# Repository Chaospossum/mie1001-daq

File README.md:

# MIE1001 Team 5&4 — data acquisition for the portable quadrupole mass spectrometer

Foundation of Imaging Engineering (MIE1001), Maastricht University, 2026.
Team 5 owns the data chain: detector signal → preamp → ADC → Arduino UNO → laptop, plus the DAC that
sends the mass command to the Extrel 150-QC quadrupole controller.

```
Faraday cup ─► preamp (LMP7721, 100 MΩ) ─► ADS1115 16-bit ADC ─I²C─► Arduino UNO ─USB─► laptop
                                               MCP4725 12-bit DAC ◄─I²C─┘ ─► mass command (0-5 V now; Extrel wants 0-10 V)
```

## Contents

| Folder | What |
|---|---|
| `firmware/` | Arduino sketches (open in the Arduino IDE; board: Arduino Uno) |
| `hardware/mie1001_daq_simple/` | **Simple shield, rev E**: plug-in ADS1115 + MCP4725 breakouts, screw terminals, and the Faraday-cup preamp. Ordered from Digi-Key and hand-soldered. See its README |
| `hardware/mie1001_daq_board/` | **Full shield, rev E**: everything soldered (ADS1115, MCP4725, preamp), BNC input, CEM/Faraday ranges |
| `hardware/enclosure/` | First idea for a 3D-printed enclosure (transparent PETG, OpenSCAD source, STLs, renders). Not printed, not a team decision yet |
| `wokwi/` | Wokwi simulation of the whole loop: Uno → MCP4725 → quadrupole stand-in → ADS1115, with custom chips written in C and a PEG1000 test spectrum |
| `data/` | Real measurements (`2026-09-20_selftest/`: first self-tests of the ADS1115 and MCP4725 on the Uno, with plots) and clearly labelled simulations (`simulations/`) |

### Firmware

| Sketch | Tests | For | Serial |
|---|---|---|---|
| `DAQ_shield_scan` | **Mass scan**: DAC code sweep on QPS OUT, preamp current (A1−A3) with 50 Hz window averaging, A2 command read-back (JP1), zero/offset, trigger on D8, self-check (`i`) | **shield** (rev E) | 115200 |
| `DAQ_loopback_test` | DAC → ADC loopback (wire QPS OUT to SIGNAL IN) | **shield** | 115200 |
| `DAQ_mini_chain` | Chain: DAC → UNO A0 → PWM D9 → RC filter → ADS1115. Assumes ADS A1 = DAC; on the shield A1 is PRE_OUT | **breadboard only** | 115200 |
| `ADS1115_selftest` | ADS1115 alone: reads the UNO's 3.3 V, GND and 5 V pins | breadboard | 9600 |
| `MCP4725_standalone_test` | MCP4725 alone, read back on the UNO's A0; scans the I²C bus if not found | breadboard | 9600 |
| `MCP4725_sine_scope` | MCP4725 sine wave, sent vs. read on the Serial Plotter | breadboard | 115200 |
| `SparkFun_MCP4725_waveform` | SparkFun's 512-point sine example (J. Bartlett, 2014, beerware). Its A2/A3 power trick is for a bare breakout on the UNO header, not the shield | breadboard (shield: drop the A2/A3 lines) | — |
| `ioannis_DAC_3V` | Ioannis's sketch: holds the MCP4725 (0x60) at 3 V. Now measures the real 5 V rail first (internal bandgap), since a fixed code 2457 gave ~2.9 V on USB | either | 115200 |
| `PwmGenerator` | Two-channel PWM generator on pins 9/10 (bench tool, not DAQ) | bench | 115200 |

Libraries: Adafruit ADS1X15, Adafruit MCP4725. I²C addresses: ADS1115 0x48, MCP4725 0x60.

### Hardware

Both boards are **generated by Python** (`generate_schematic.py`, `generate_pcb.py`); `./build.sh` rebuilds the
KiCad files, runs ERC, DRC (with schematic parity) and the preamp guard check, and writes the fab files in
`fab/` (gerbers, Digi-Key BOM; the JLCPCB files are optional leftovers). Edits made in the KiCad GUI are overwritten by the next build. Needs KiCad 10 (flatpak `org.kicad.KiCad`).
The simple board's PCB script reuses the router in `../mie1001_daq_board/`, so keep both folders side by side.

## Status (2026-09-25)

- Firmware: all sketches compile for the UNO. The self-tests pass on the real Uno (see `data/`);
  `DAQ_shield_scan` is untested until the shield is soldered.
- Simple shield rev E: fixes from an independent design review (closed guard ring under the LMP7721, mask-free
  guard, 100k/100k VREF divider, A4/A5 wired, JP1 mass-command read-back). ERC, DRC and guard check clean.
  Not yet ordered. Everything is ordered from Digi-Key and soldered by hand. Do a 1:1 paper print check on a real UNO first.
- Open: the Extrel 150-QC mass command is 0-10 V (a x2 stage with its own supply is still needed) and its
  volts-per-amu scaling is unconfirmed.

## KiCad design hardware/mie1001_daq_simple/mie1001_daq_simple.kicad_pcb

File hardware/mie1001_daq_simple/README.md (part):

# MIE1001 — simple DAQ shield (rev E)

The beginner version of the DAQ board: an Arduino UNO R3 shield that the two breakout
boards from class plug into (modular: both unplug). Fat tracks, the breakouts, connectors and
through-hole parts are hand-soldered. **Rev D adds a Faraday-cup preamp** with 16 small SMD parts.
**Everything is ordered from Digi-Key** (university procurement, see [Ordering from Digi-Key](#ordering-from-digi-key))
**and hand-soldered** (see [Hand-soldering order](#hand-soldering-order)); JLCPCB assembly is an optional alternative.

```
SIGNAL IN (J1) -> R2 4k7 -> [CR1/CR2 clamp, C1 filter] -> ADS1115 breakout A0 -> I2C -> UNO -> USB -> laptop
UNO -> I2C -> SparkFun MCP4725 breakout OUT -> QPS OUT (J2), 0-5 V  (JP1, bridged: also -> ADS1115 A2 read-back)
TRIG IN (J3) -> R1 1k -> UNO D8 (R3 100k to GND)    ADS1115 ALRT -> UNO D2
Faraday cup -> J5 SMA -> R4 10k -> CR3 clamp to VREF -> R5 1k -> U3 LMP7721 preamp (R6 100M || C2 10p)
            -> R11/C6 1k/1u -> ADS1115 A1 (PRE_OUT)      VREF 2.5 V (R8/R9 100k/100k + C4 -> U4A MCP6002 -> R10 -> C5) -> A3
J4 = test header: 1 PRE_OUT, 2 A2 (QPS read-back while JP1 is bridged), 3 VREF, 4 GND
I2C: UNO SDA/SCL header pins AND A4/A5 (rev E)
```

| Check | Result |
|---|---|
| ERC | 0 errors, 0 warnings |
| Guard check (`check_guard.py`, rev E) | PASS: 0 items of any other net within 1.0 mm of the preamp input (COAX_IN, DET_IN, TIA_IN, TIA_REF), every input item has guard copper within 0.6 mm, and the bare-board flood fill from the input reaches only VREF and TIA_OUT on F.Cu and only VREF on B.Cu. The same script FAILS on the rev D board (7 leakage paths), so it catches the rev D defect |
| Independent critical review | Two reviews against the Adafruit, SparkFun, Arduino, Phoenix and TI source files and datasheets. Rev A: pinouts and UNO geometry correct, four fixes → rev B. Rev C: copper clean, no respin needed; one wrong BOM part number and several wrong claims in this file, all corrected below |
| Host board | Arduino UNO R3 **SMD** (ATmega328P in a flat TQFP-32 package). Its headers are identical to the standard R3 (same positions, same pins, SDA/SCL next to AREF), so the shield fits unchanged |
| Still unverified | The height of the parts on the UNO under the shield (crystal, USB chip, capacitors). The SMD chip itself is only about 1.2 mm tall, so this is much less of a risk than with the socketed DIP chip, but look at your board before soldering |
| DRC incl. schematic parity | 0 errors, 0 unconnected, 0 parity issues (4 `lib_footprint_mismatch` warnings: ARD1 and J1–J3 are deliberately modified copies) — rev E |
| Orientation | Same real-UNO geometry as the full board (rev E): flipped library footprint, keep-outs over the USB, DC jack and both ICSP headers |
| Rules | 0.5 mm tracks, ≥ 0.3 mm gaps, 0.8/0.4 mm vias: far above the Digi-Key PCB Builder (5 mil / 8 mil) and JLCPCB minimums |

## What changed in rev E (2026-09-25)

An independent review of rev D found a leakage path and a few smaller problems. **No connector,
socket or mounting hole moved** (J1–J5, the two breakout sockets, H1–H3 are where they were in rev D).
The router re-laid most of the signal tracks because the obstacles changed; that does not matter
electrically, DRC and the guard check are clean.

- **Guard closed under U3.** In rev D the guard pour stopped halfway under the LMP7721, and TIA_OUT
  ran from the feedback parts under the chip body to pin 4. The copper-free gap alongside it was a
  bare-board path from the input to GND (pin 3) and +5V (pin 6). Now a VREF bar runs under the
  chip from pin 2 to pin 7 (both N/C pins, on the guard), so the input pins 1 and 8 sit in a closed
  guard pocket, and TIA_OUT leaves the guard on the **bottom layer only**: via next to R6/C2, under
  the chip, via below the bar, then to pin 4 and R11. On the top layer the input is now completely
  surrounded by guard copper; the only other net it faces is TIA_OUT across C2 and R6 themselves,
  which only adds in parallel with the feedback resistor (TI LMP7721 datasheet, 10.1).
  DET_IN was re-laid as two straight runs so the guard hugs it everywhere.
- **No solder mask on the guard (both layers).** The mask openings are the guard pour shrunk by
  0.10 mm and kept ≥ 0.50 mm from any pad and ≥ 0.40 mm from any track of another net, and off all
  silkscreen. So every other track, every gap next to the guard and the edge of the GND pour stay
  under mask: exposed guard copper is never closer than 0.4 mm (mask web) to exposed copper of
  another net, which keeps solder bridges unlikely. Care points: the SMA J5 ground pins sit next to
  the bare guard ring around the centre pin (≥ 0.5 mm mask web); don't flood them with solder, and
  check there is no bridge from a J5 ground pin to the ring before powering up.
- **`check_guard.py` is strict now.** It fails (exit 1) on any unguarded input item (it used to only
  print them) and adds a bare-board flood fill from the input nets on each copper layer: reaching
  copper of any net other than VREF / TIA_OUT, or leaving the guard area, fails the build.
  `check_guard.py .history/revD-final/mie1001_daq_simple.kicad_pcb` shows the rev D failure.
- **Quieter VREF.** R8/R9 are now 100k/100k (were 10k/10k). With C4 10 µF the divider's corner is
  0.32 Hz instead of 3.2 Hz, so 50 Hz ripple on the USB 5 V reaches VREF attenuated ~160× instead
  of ~16×. The MCP6002's ~1 pA input bias current makes no measurable error through 50k.
- **A4/A5 also carry SDA/SCL.** On a genuine UNO R3 they are the same signals as the SDA/SCL pins
  next to AREF; some clones don't have those two pins, and then the shield works through A4/A5.
  Consequence: **never use A4/A5 as analog inputs** with this shield fitted.
- **JP1, QPS read-back.** A solder jumper, bridged by a copper strip from the factory, connects
  QPS OUT (MCP4725 OUT, J2) to ADS1115 **A2** (J4 pin 2). The firmware can read the command voltage
  it actually set: `ads.readADC_SingleEnded(2)`, with the ±6.144 V range
  (`ads.setGain(GAIN_TWOTHIRDS)`), because 0–5 V does not fit the ±4.096 V range. To use A2 for something else, cut the thin copper
  bridge between JP1's pads with a knife (check with a meter); a blob of solder closes it again.
  JP1 is next to J4, marked "JP1 / A2=QPS".
- **C5/C6 part (optional JLC route only).** LCSC C15849 had no LCSC stock; now C5673 (Samsung CL10A105KA8NNNC, 1 µF 25 V X5R
  0603, extended part: one extra JLC loading fee). There is no other *basic* 1 µF 0603 at JLC;
  JLC's own library still listed C15849 in stock on 2026-09-25, so it is a valid fallback.
- **Docs:** J4 firmware note rewritten (pins 1 and 3 are op-amp outputs), wrong 8 SPS/mains claim
  corrected, comparison with the full board corrected, U3 "no solder mask" note is now true.

## What changed in rev D (2026-09-24): the preamp

The Faraday cup gives a current of pA to nA. The ADS1115 measures voltage, so rev D adds a
**transimpedance amplifier** (U3, LMP7721) that turns 1 nA into 0.1 V. Everything that was on rev C
stays where it was; the preamp sits in the band under the digital header, where the text used to be
(the text moved to the left edge and the back).

| Part | Job |
|---|---|
| **J5** SMA jack (vertical, PTFE) | Detector input. Use a **BNC-female to SMA-male adapter** for a BNC cable. A BNC did not fit anywhere on this board |
| **U3** LMP7721 + **R6** 100 MΩ | The preamp: Vout = VREF − I × 100 MΩ. Full scale ~25 nA; 1 ADC count = 1.25 pA at GAIN_ONE |
| **C2** 10 pF | Stops the preamp oscillating with the cable capacitance. Sets a 159 Hz bandwidth |
| **R4** 10k + **CR3** BAV199 + **R5** 1k | Protect U3 from a discharge on the cable. CR3 is tied to VREF, so it leaks ~0 into the input |
| **VREF** 2.5 V: R8/R9 100k/100k (rev E), C4 10 µF, U4A MCP6002, R10 100 Ω, C5 1 µF | The input sits at 2.5 V so the output can swing both ways on a single 5 V supply |
| **R7** 1k | Protects U3's + input |
| **R11** 1k + **C6** 1 µF | 159 Hz anti-alias filter before ADS1115 **A1** |
| **Guard ring** (copper at VREF, both layers, no solder mask) | Surrounds the whole input so no other copper can leak pA into it; closed under U3 between pins 2 and 7 (rev E) |

**Firmware:** read the preamp as `ads.readADC_Differential_1_3()` (A1 − A3 = PRE_OUT − VREF), then
`I = −V / 100e6`. The ADS1115 only offers the pairs 0-1, 0-3, 1-3 and 2-3, which is why VREF is on A3.
SIGNAL IN (J1) → A0 still works as before for a voltage input.

**J4 changed:** pin 1 is now PRE_OUT and pin 3 is VREF (monitor only: connect a meter or scope, never a
source). Pin 2 (A2) carries the QPS read-back while JP1 is bridged (rev E); cut JP1 to use it as a free input.

**Still 0-5 V on QPS OUT.** The Extrel 150-QC wants a 0-10 V mass command; that needs a gain-2 amplifier on
a supply above 10 V (e.g. a 12 V adapter on the UNO's DC jack). Not on this revision.

**Handling:** the input works at picoamps. After soldering, wash off **all** flux around U3, R6, C2, R4 and
J5 (isopropyl alcohol, then dry), handle the board by its edges, and measure the zero offset with the
cable connected and the beam off before every scan.

## Names on the drawing and the board (2026-09-24, copper unchanged)

- The UNO is **ARD1** and the clamp diodes are **CR1, CR2** (were A1, D1, D2), so the names no longer clash
  with the UNO's pins A1 and D2.
- The UNO symbol shows only the pin names printed on the UNO (D2, D8, SDA ...), not KiCad pad numbers.
- SDA/A4 and SCL/A5 are the same signals on the UNO R3. Since rev E the shield connects A4/A5 as well
  (for clones without the SDA/SCL pins), so never use A4 and A5 as analog inputs.

## What changed in rev C

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
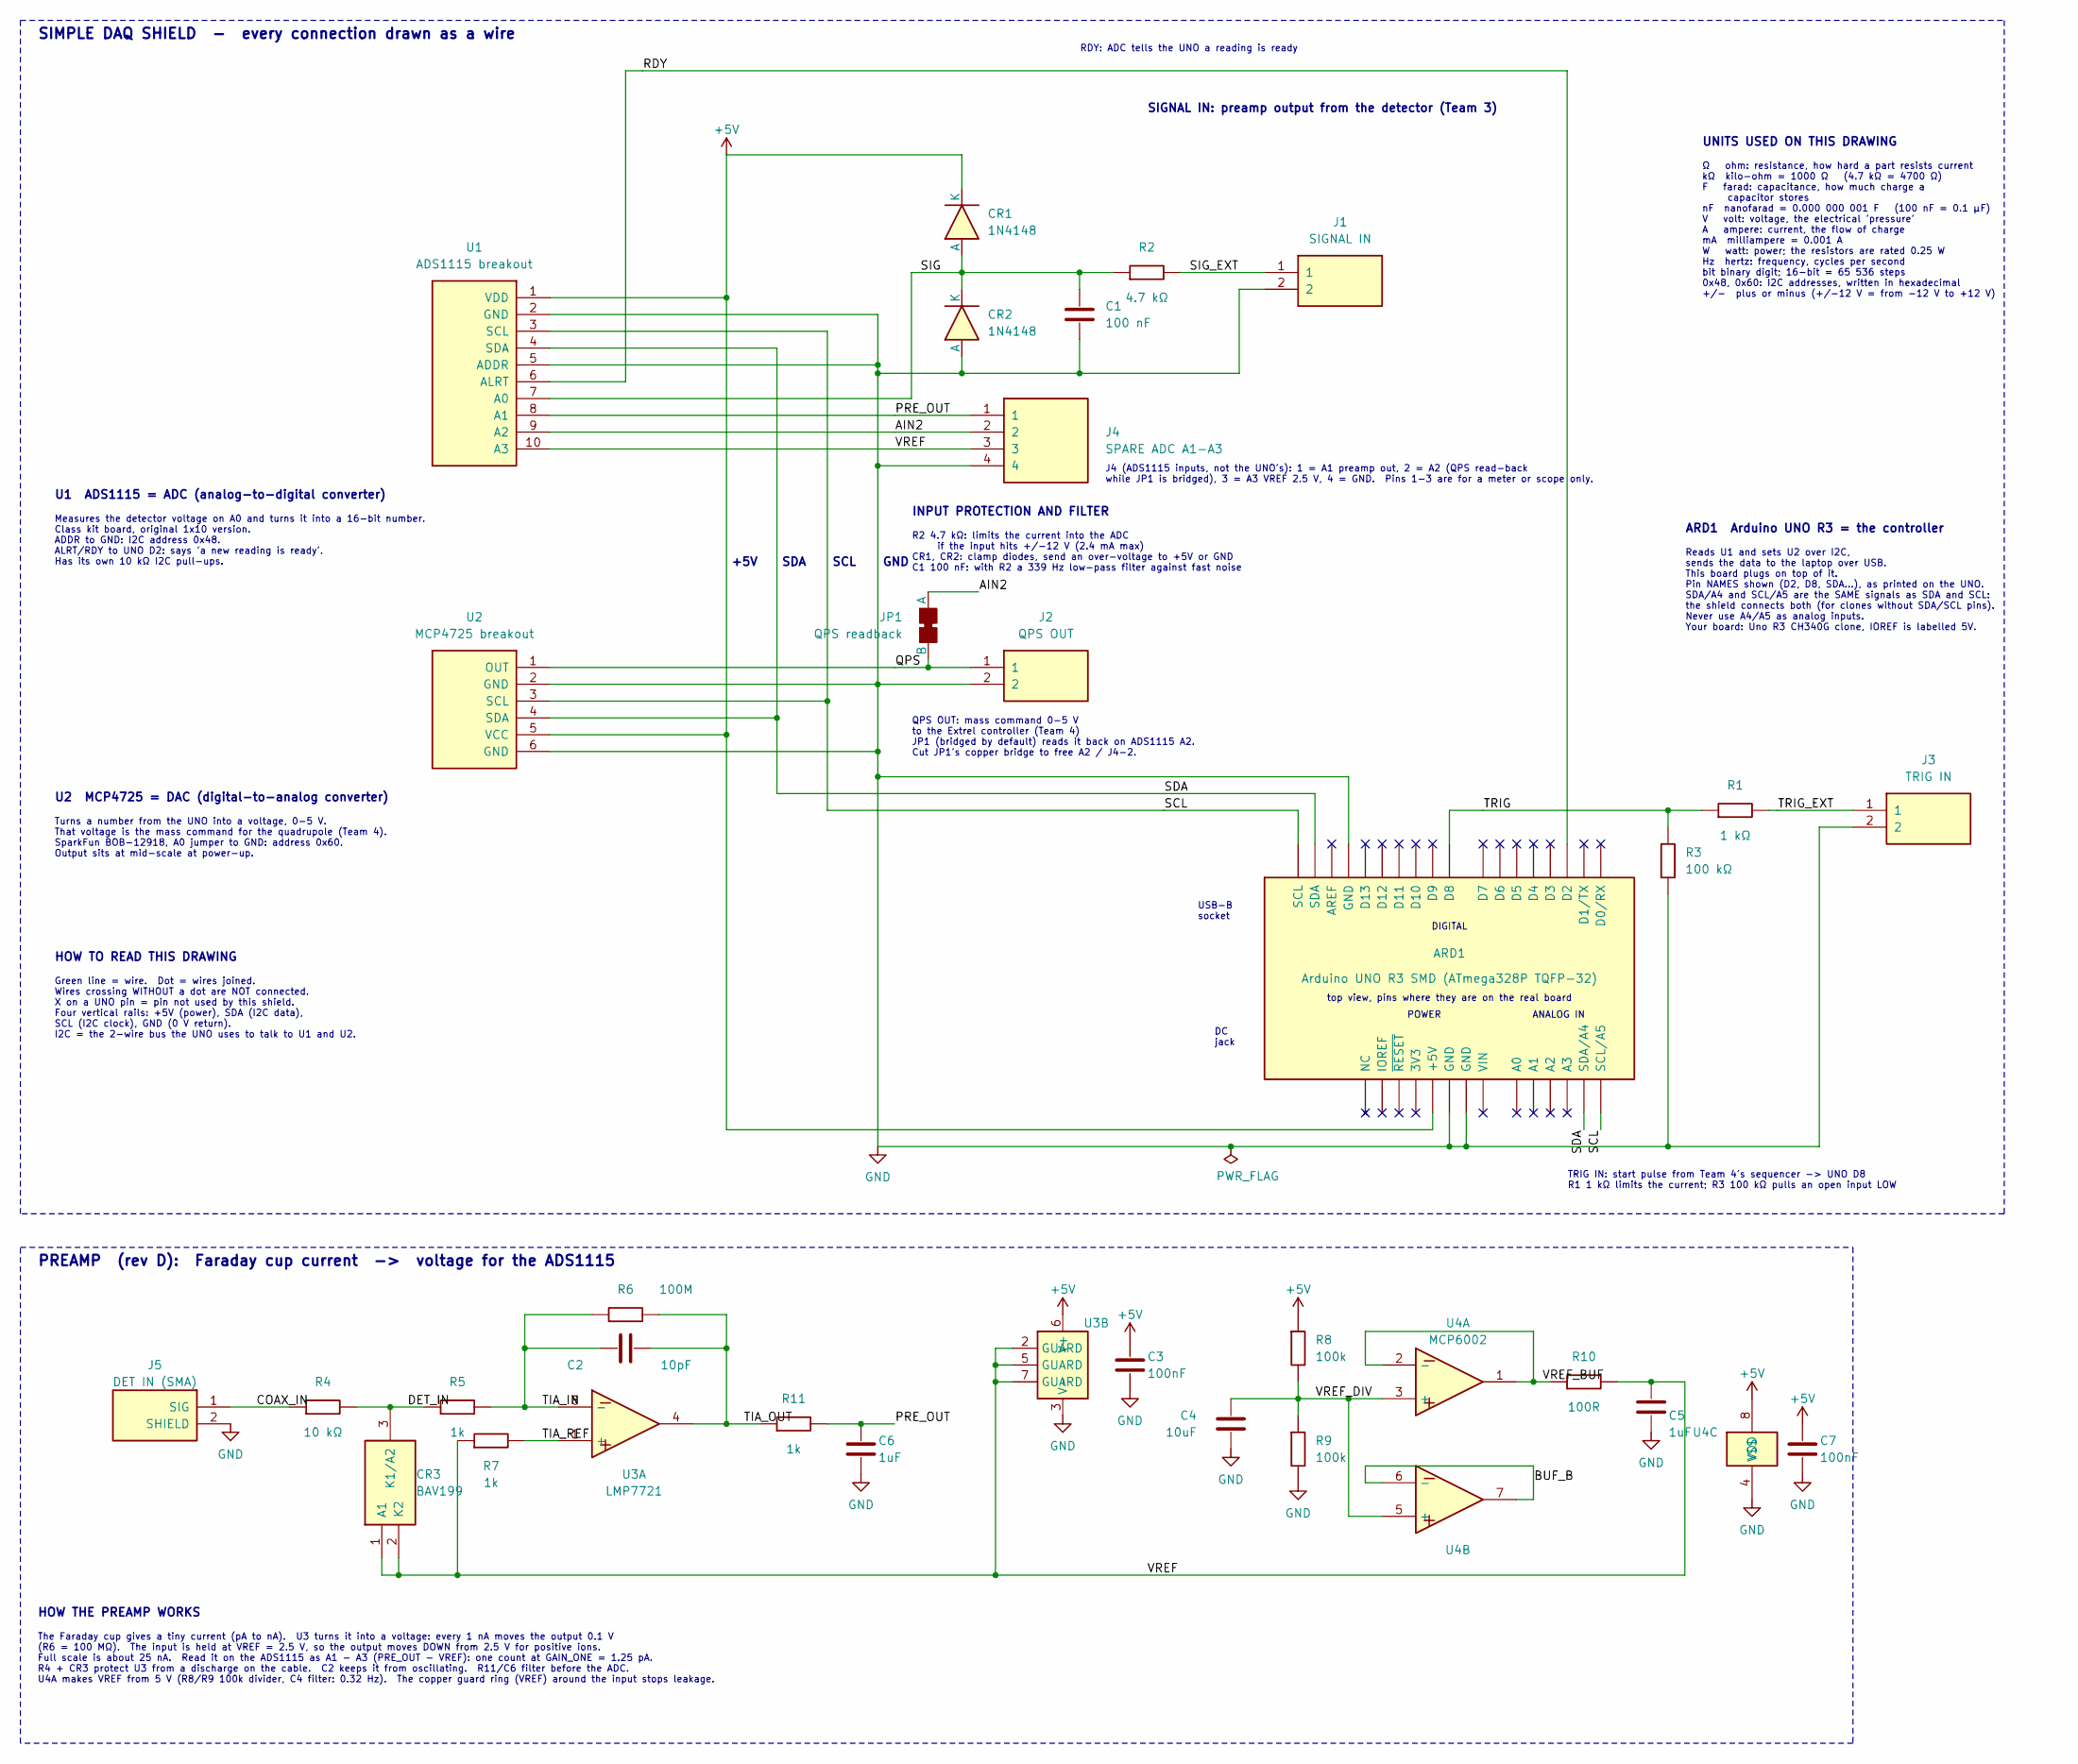
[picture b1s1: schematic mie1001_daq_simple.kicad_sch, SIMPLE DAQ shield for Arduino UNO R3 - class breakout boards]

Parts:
ARD1: Arduino UNO R3 SMD (ATmega328P TQFP-32); Arduino_UNO_R3; Rating Arduino UNO R3 SMD (ATmega328P TQFP-32); MPN UNO R3 SMD CH340 clone (marked V1888); 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; Digi-Key P/N do not order: use your own board
C1: 100 nF; C_Disc_D5.0mm_W2.5mm_P2.50mm; Rating 100 nF 50 V X7R ceramic; MPN K104K15X7RF5TL2; Digi-Key P/N BC1084CT-ND
C2: 10pF; C_0603_1608Metric; Rating 10pF C0G 50V 0603; MPN CL10C100JB8NNNC; Digi-Key P/N 1276-1027-1-ND
C3, C7: 100nF; C_0603_1608Metric; Rating 100nF X7R 50V 0603; MPN 885012206095; Digi-Key P/N 732-8013-1-ND
C4: 10uF; C_0805_2012Metric; Rating 10uF X5R 25V 0805; MPN TMK212BBJ106KGHT; Digi-Key P/N 587-4334-1-ND
C5, C6: 1uF; C_0603_1608Metric; Rating 1uF X5R 25V 0603; MPN CL10A105KA8NNNC; Digi-Key P/N 1276-1102-1-ND
CR1, CR2: 1N4148; D_DO-35_SOD27_P7.62mm_Horizontal; Rating 1N4148; MPN 1N4148; Digi-Key P/N 1N4148FS-ND
CR3: BAV199; SOT-23; Rating BAV199LT1G; MPN BAV199LT1G; Digi-Key P/N BAV199LT1GOSCT-ND
J1: SIGNAL IN; TerminalBlock_Phoenix_PT-1,5-2-3.5-H_1x02_P3.50mm_Horizontal; Rating Signal in; MPN 1984617; Digi-Key P/N 277-1721-ND
J2: QPS OUT; TerminalBlock_Phoenix_PT-1,5-2-3.5-H_1x02_P3.50mm_Horizontal; Rating QPS out; MPN 1984617; Digi-Key P/N 277-1721-ND
J3: TRIG IN; TerminalBlock_Phoenix_PT-1,5-2-3.5-H_1x02_P3.50mm_Horizontal; Rating Trigger in; MPN 1984617; Digi-Key P/N 277-1721-ND
J4: SPARE ADC A1-A3; PinSocket_1x04_P2.54mm_Vertical; Rating Spare ADC in; MPN PPTC041LFBN-RC; Digi-Key P/N S7002-ND
J5: DET IN (SMA); SMA_Amphenol_132134_Vertical; Rating Detector in, SMA jack vertical; MPN 132134; Digi-Key P/N ACX1230-ND
JP1: QPS readback; SolderJumper-2_P1.3mm_Bridged_RoundedPad1.0x1.5mm
R1: 1 kΩ; R_Axial_DIN0207_L6.3mm_D2.5mm_P10.16mm_Horizontal; Rating 1 kOhm 0.25 W; MPN CFR-25JB-52-1K; Digi-Key P/N 1.0KQBK-ND
R2: 4.7 kΩ; R_Axial_DIN0207_L6.3mm_D2.5mm_P10.16mm_Horizontal; Rating 4.7 kOhm 0.25 W; MPN CFR-25JB-52-4K7; Digi-Key P/N 13-CFR-25JB-52-4K7-ND
R3: 100 kΩ; R_Axial_DIN0207_L6.3mm_D2.5mm_P2.54mm_Vertical; Rating 100 kOhm 0.25 W; MPN CFR-25JB-52-100K; Digi-Key P/N 13-CFR-25JB-52-100K-ND
R4: 10 kΩ; R_Axial_DIN0207_L6.3mm_D2.5mm_P2.54mm_Vertical; Rating 10 kOhm 0.25 W; MPN CFR-25JB-52-10K; Digi-Key P/N 13-CFR-25JB-52-10K-ND
R5, R7, R11: 1k; R_0603_1608Metric; Rating 1k 1% 0603; MPN RC0603FR-071KL; Digi-Key P/N 311-1.00KHRCT-ND
R6: 100M; R_1206_3216Metric; Rating 100M 1% 1206; MPN HVCB1206FKC100M; Digi-Key P/N HVCB1206FKC100MCT-ND
R8, R9: 100k; R_0603_1608Metric; Rating 100k 1% 0603; MPN RC0603FR-07100KL; Digi-Key P/N 311-100KHRCT-ND
R10: 100R; R_0603_1608Metric; Rating 100R 1% 0603; MPN RC0603FR-07100RL; Digi-Key P/N 311-100HRCT-ND
U1: ADS1115 breakout; PinSocket_1x10_P2.54mm_Vertical; Rating Adafruit ADS1115 breakout (original, 1x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; MPN 1085 (ORIGINAL 1x10 version, from the c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; Digi-Key P/N do not order
U2: MCP4725 breakout; PinSocket_1x06_P2.54mm_Vertical; Rating SparkFun MCP4725 breakout; MPN 12918; Digi-Key P/N 1568-12918-ND
U3: LMP7721; SOIC-8_3.9x4.9mm_P1.27mm; Rating LMP7721MA/NOPB; MPN LMP7721MA/NOPB; Digi-Key P/N LMP7721MA/NOPB-ND
U4: MCP6002; SOIC-8_3.9x4.9mm_P1.27mm; Rating MCP6002-I/SN; MPN MCP6002-I/SN; Digi-Key P/N MCP6002-I/SN-ND

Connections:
+5V: ARD1.5 (+5V), C3.1, C7.1, CR1.1 (K), R8.1, U1.1 (VDD), U2.5 (VCC), U3.6 (V+), U4.8 (VDD)
/AIN2: J4.2, JP1.1 (A), U1.9 (A2)
/BUF_B: U4.6 (-), U4.7
/COAX_IN: J5.1 (SIG), R4.1
/DET_IN: CR3.3 (K1/A2), R4.2, R5.1
/PRE_OUT: C6.1, J4.1, R11.2, U1.8 (A1)
/QPS: J2.1, JP1.2 (B), U2.1 (OUT)
/RDY: ARD1.17 (D2), U1.6 (ALRT)
/SCL: ARD1.14 (SCL/A5), ARD1.32 (SCL), U1.3 (SCL), U2.3 (SCL)
/SDA: ARD1.13 (SDA/A4), ARD1.31 (SDA), U1.4 (SDA), U2.4 (SDA)
/SIG: C1.1, CR1.2 (A), CR2.1 (K), R2.1, U1.7 (A0)
/SIG_EXT: J1.1, R2.2
/TIA_IN: C2.1, R5.2, R6.1, U3.8 (-)
/TIA_OUT: C2.2, R6.2, R11.1, U3.4
/TIA_REF: R7.2, U3.1 (+)
/TRIG: ARD1.23 (D8), R1.1, R3.1
/TRIG_EXT: J3.1, R1.2
/VREF: C5.1, CR3.1 (A1), CR3.2 (K2), J4.3, R7.1, R10.2, U1.10 (A3), U3.2 (GUARD), U3.5 (GUARD), U3.7 (GUARD)
/VREF_BUF: R10.1, U4.1, U4.2 (-)
/VREF_DIV: C4.1, R8.2, R9.1, U4.3 (+), U4.5 (+)
GND: ARD1.6 (GND), ARD1.7 (GND), ARD1.29 (GND), C1.2, C3.2, C4.2, C5.2, C6.2, C7.2, CR2.2 (A), J1.2, J2.2, J3.2, J4.4, J5.2 (SHIELD), R3.2, R9.2, U1.2 (GND), U1.5 (ADDR), U2.2 (GND), U2.6 (GND), U3.3 (V-), U4.4 (VSS)

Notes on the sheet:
SIMPLE DAQ SHIELD - every connection drawn as a wire
USB-B socket
DC jack
top view, pins where they are on the real board
POWER
ANALOG IN
DIGITAL
U1 ADS1115 = ADC (analog-to-digital converter)
Measures the detector voltage on A0 and turns it into a 16-bit number. Class kit board, original 1x10 version. ADDR to GND: I2C address 0x48. ALRT/RDY to UNO D2: says 'a new reading is ready'. Has its own 10 kΩ I2C pull-ups.
U2 MCP4725 = DAC (digital-to-analog converter)
Turns a number from the UNO into a voltage, 0-5 V. That voltage is the mass command for the quadrupole (Team 4). SparkFun BOB-12918, A0 jumper to GND: address 0x60. Output sits at mid-scale at power-up.
HOW TO READ THIS DRAWING
Green line = wire. Dot = wires joined. Wires crossing WITHOUT a dot are NOT connected. X on a UNO pin = pin not used by this shield. Four vertical rails: +5V (power), SDA (I2C data), SCL (I2C clock), GND (0 V return). I2C = the 2-wire bus the UNO uses to talk to U1 and U2.
+5V
SDA
SCL
GND
ARD1 Arduino UNO R3 = the controller
Reads U1 and sets U2 over I2C, sends the data to the laptop over USB. This board plugs on top of it. Pin NAMES shown (D2, D8, SDA...), as printed on the UNO. SDA/A4 and SCL/A5 are the SAME signals as SDA and SCL: the shield connects both (for clones without SDA/SCL pins). Never use A4/A5 as analog 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
SIGNAL IN: preamp output from the detector (Team 3)
RDY: ADC tells the UNO a reading is ready
UNITS USED ON THIS DRAWING
Ω ohm: resistance, how hard a part resists current kΩ kilo-ohm = 1000 Ω (4.7 kΩ = 4700 Ω) F farad: capacitance, how much charge a capacitor stores nF nanofarad = 0.000 000 001 F (100 nF = 0.1 µF) V volt: voltage, the electrical 'pressure' A ampere: current, the flow of charge mA milliampere = 0.001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
INPUT PROTECTION AND FILTER
R2 4.7 kΩ: limits the current into the ADC if the input hits +/-12 V (2.4 mA max) CR1, CR2: clamp diodes, send an over-voltage to +5V or GND C1 100 nF: with R2 a 339 Hz low-pass filter against fast noise
J4 (ADS1115 inputs, not the UNO's): 1 = A1 preamp out, 2 = A2 (QPS read-back while JP1 is bridged), 3 = A3 VREF 2.5 V, 4 = GND. Pins 1-3 are for a meter or scope only.
QPS OUT: mass command 0-5 V to the Extrel controller (Team 4) JP1 (bridged by default) reads it back on ADS1115 A2. Cut JP1's copper bridge to free A2 / J4-2.
TRIG IN: start pulse from Team 4's sequencer -> UNO D8 R1 1 kΩ limits the current; R3 100 kΩ pulls an open input LOW
PREAMP (rev D): Faraday cup current -> voltage for the ADS1115
HOW THE PREAMP WORKS
The Faraday cup gives a tiny current (pA to nA). U3 turns it into a voltage: every 1 nA moves the output 0.1 V (R6 = 100 MΩ). The input is held at VREF = 2.5 V, so the output moves DOWN from 2.5 V for positive ions. Full scale is about 25 nA. Read it on the ADS1115 as A1 - A3 (PRE_OUT - VREF): one 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

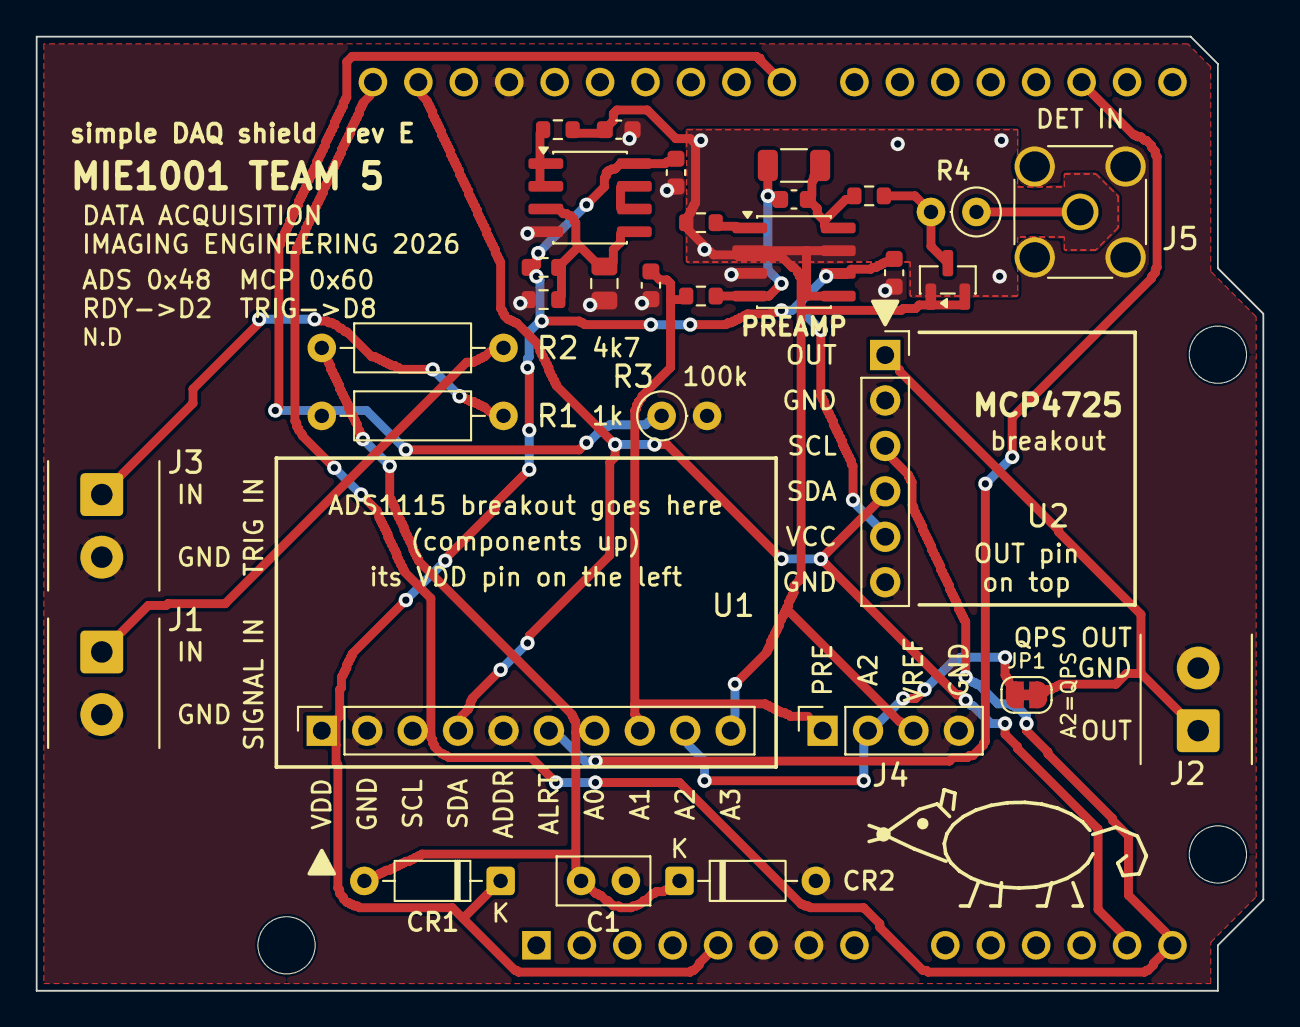
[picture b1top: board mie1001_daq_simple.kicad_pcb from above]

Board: 2 copper layers, 68.6 x 53.3 mm, 35 parts (1 on the bottom side), 21 nets.

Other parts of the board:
H1, H2, H3: MountingHole_3.2mm_M3

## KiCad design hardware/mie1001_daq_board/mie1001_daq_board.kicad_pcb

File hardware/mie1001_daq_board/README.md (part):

# MIE1001 Team 5 — DAQ shield for Arduino UNO R3 (rev E)

Data-acquisition shield for the portable quadrupole mass spectrometer. It measures the
detector current (pA to µA) with an electrometer transimpedance amplifier and a 16-bit
ADC, and drives the QPS mass command with a 12-bit DAC. It plugs onto an Arduino UNO R3
and takes all power from the UNO's 5 V rail.

```
detector -> J1 BNC -> R14 10k -> D1 clamp to VREF -> R4 1k -> U4 LMP7721 TIA (2M2 / 100M via JP1)
         -> R3/C2 1k/1uF anti-alias -> U2 ADS1115 AIN0 (AIN1 = VREF via R16/C10) -> I2C -> UNO -> USB
VREF: R7/R8 divider + C3 10uF -> U3B buffer -> R15 100R -> VREF + C9 1uF (-> R17 -> U4 IN+, guard, D1)
UNO -> I2C -> U1 MCP4725 -> U3A MCP6002 buffer -> R12 100R -> J2 -> Extrel QPS mass command
                                                          \-> R13 -> ADS1115 AIN2 (read-back)
Team 4 sequencer -> J4 -> R9/R10 -> UNO D8 (trigger)     U2 ALERT/RDY -> R11 pull-up -> UNO D2
```

## Status

| Check | Result |
|---|---|
| ERC (schematic) | 0 errors, 0 warnings |
| DRC (layout), incl. schematic parity | 0 errors, 0 unconnected, 0 parity issues |
| DRC warnings left | 4 × `lib_footprint_mismatch`: J1, J2, J4, A1 are deliberately modified copies (see *Layout*) |
| Guard check (`check_guard.py`) | 0 unexpected items: no copper of any other net within 1.0 mm of BNC_IN / DET_IN / TIA_IN / TIA_REF, except the BNC's own shell pins (0.98 mm, connector geometry). 22 input items have no VREF guard copper within 0.6 mm: R14.1 and the BNC centre-pin trace (squeezed between the BNC's pins), JP1.2, and 19 segments of the TIA_IN run from C1 to JP1. Those are bordered by the feedback nets (TIA_OUT, RF_100M), whose leakage only adds in parallel with the feedback resistor, not by +5 V or GND |
| Orientation | Matches a real UNO R3 seen from the top (rev D was mirrored, see below). **Still do the 1:1 paper check** |
| SMD parts | JLC assembles 31 parts (15 BOM lines). **R14 is hand-soldered** from the Digi-Key order (anti-surge, no verified LCSC stock). C15849 (1 µF, JLC *basic*) showed no stock on LCSC's shop on 2026-09-22 and the LMP7721 (C124427) only ~60 pcs: confirm both when ordering |

## Files

| File | What it is |
|---|---|
| `generate_schematic.py` | writes the schematic, symbol library and `BOM.csv` |
| `generate_pcb.py` | writes the PCB: placement, routing (built-in grid router), guard and ground pours |
| `check_guard.py` | leakage check around the pA input node |
| `make_fab.py` | JLCPCB BOM/CPL + gerber zip |
| `build.sh` | runs all of the above plus ERC, DRC and the exports |
| `mie1001_daq_board.kicad_pro/.kicad_sch/.kicad_pcb` | the KiCad 10 project (open the `.kicad_pro`) |
| `mie1001_daq_board.pdf` | schematic plot |
| `BOM.csv` | full BOM: manufacturer, MPN, Digi-Key P/N **and LCSC P/N** |
| `fab/mie1001_daq_shield_gerbers.zip` | gerbers + drill, upload this to JLCPCB |
| `fab/jlcpcb_bom.csv`, `fab/jlcpcb_cpl.csv` | JLCPCB assembly BOM and pick-and-place |
| `fab/assembly_top.pdf`, `fab/board_top.png` | assembly drawing and render |

**Both files are generated.** Edit the Python, then run `./build.sh`. Editing the
`.kicad_sch`/`.kicad_pcb` in the GUI works, but the next `./build.sh` overwrites it.

## What changed in rev E (independent critical review, 2026-09-22)

| Change | Why |
|---|---|
| **Board no longer mirrored** | KiCad's `Module:Arduino_UNO_R3` footprint is drawn from the back (kicad-footprints #864). Rev D used it as-is, so its headers, jacks and holes were a mirror image of a real UNO and the shield could not plug in. The footprint is now flipped and every coordinate goes through the corrected transform. The central block's *placement* was moved as one piece (a translation as seen from the top, so parts keep their positions relative to each other); all *routing* was redone and every check was re-run on rev E |
| **R14 10k anti-surge** (Panasonic ERJ-PA3F1002V, AEC-Q200, pulse-rated) between the BNC and the clamp | A discharge on the BNC went straight through D1 into VREF. R14 limits it; drop is 10 µV per nA. A plain thick-film 0603 was not rated for the pulse; a 1206 would not fit without crossing the input traces |
| **VREF buffered and decoupled**: R15 100 Ω + C9 1 µF, C3 100 nF → 10 µF | VREF had no capacitor and fed the LMP7721 IN+, AIN1 and the clamp directly; USB ripple passed the divider |
| **R17 1k into LMP7721 IN+**, **R16/C10 1k/1 µF into AIN1** | IN+ protection; AIN1 now sees the same 1k/1 µF as AIN0, so the ADC input offsets match |
| **LMP7721 pin 5 (N/C) on the guard** | It floated next to the input |
| Router keeps every other net ≥1.2 mm from the input nets | The review found the RDY track 0.23 mm from the BNC centre pin; `check_guard.py` now names every nearby item and fails on anything unexpected |
| Guard widened around IN+ and the BNC centre pin | Ground pour was 0.7–0.94 mm from input copper |
| Silkscreen ≥ 1.0 mm text | 0.8 mm was below the legible minimum |
| BNC mounting pegs stay unconnected | They are unnumbered pads with no schematic pin (netting them breaks the parity check); the shell is grounded through pins 2–4 |
| **Outline corner fixed** (second review) | The lower-right chamfer had been copied wrong since rev D: it now runs (38.1, 0) → (40.64, 2.54) like the UNO drawing |
| **Keep-outs** over the 328P ICSP header moved/enlarged, one added over the 16U2's ICSP1 header; keep-outs now respect a via's/track's full width; all vias tented | Second review: the ICSP keep-out was offset, and +5 V vias sat untented above ICSP1 |
| **JLCPCB rotations corrected** in `fab/jlcpcb_cpl.csv`: SOIC +270°, SOT-23/SOT-23-6 −90° (JLCKicadTools table) | Raw KiCad angles would place U1, U3, U4 and D1 90° off. **The MSOP (U2) has no known offset: check it in JLC's preview** |
| BNC and block moved 0.6 mm down, J1 label beside the BNC, guard stitching vias always placed (6) | BNC pegs clear the ICSP header; a stitching via could previously be skipped silently |

### Input bias: the one trade-off kept on purpose
The TIA holds its input at VREF = 2.5 V, while the BNC shell, the cable shield and the
vacuum chamber are at GND. Any insulation between the detector wire and ground (cable,
feedthrough, detector mount) therefore sees 2.5 V and leaks 2.5 pA per TΩ into the
measurement. With PTFE coax (~10¹⁴–10¹⁵ Ω) that is ~0.003–0.03 pA; a clean dry feedthrough
~0.25 pA; a dirty or humid one a few pA. It is a near-constant offset that the per-scan
beam-off baseline removes. Moving the input to 0 V needs a negative supply (charge pump) next
to the pA node, which was judged not worth the risk. **Measure it at bring-up** (step 7).

## What changed from rev C (datasheet check, 2026-09-22)

| Change | Why | Source |
|---|---|---|
| TIA op-amp MCP6004 → **LMP7721** (U4) | MCP600x input bias is ~1 pA typical with **no max**, rising to ~19 pA at 85 °C: as large as one ADC count (0.625 pA at ±2.048 V on 100 MΩ). LMP7721: **±20 fA max** at 25 °C, Vos 150 µV max | TI SNOSAW6E Table 6.6; Microchip DS20001733L |
| **D1 clamp tied to VREF** instead of GND/5 V | At 2.5 V reverse bias each BAV199 diode leaks ~20–50 pA straight into the measured current. At 0 V bias the leakage is ~0. Still clamps at VREF ± 0.6 V | onsemi BAV199LT1G Fig. 4 |
| Quad MCP6004 → **dual MCP6002** (U3) | Only two buffers are left (DAC, VREF); no unused sections to terminate | DS20001733L Table 3-1 |
| R3/C2 10k/100nF → **1k/1µF** | Same 159 Hz corner, but the ADS1115 input current through 10k made a ~4 mV offset (~40 pA equivalent) | TI SBAS444 §5.5 |
| **R12 100 Ω** on the QPS output | MCP6002 driving >100 pF of cable needs an isolation resistor | DS20001733L §4.3 |
| **AIN2 reads the QPS output back** (via R13) | The DAC's reference is the USB 5 V rail (±5 %). The ADS1115 has its own reference, so firmware can measure what the QPS really gets | MCP4725 DS22039D §5.3 |
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
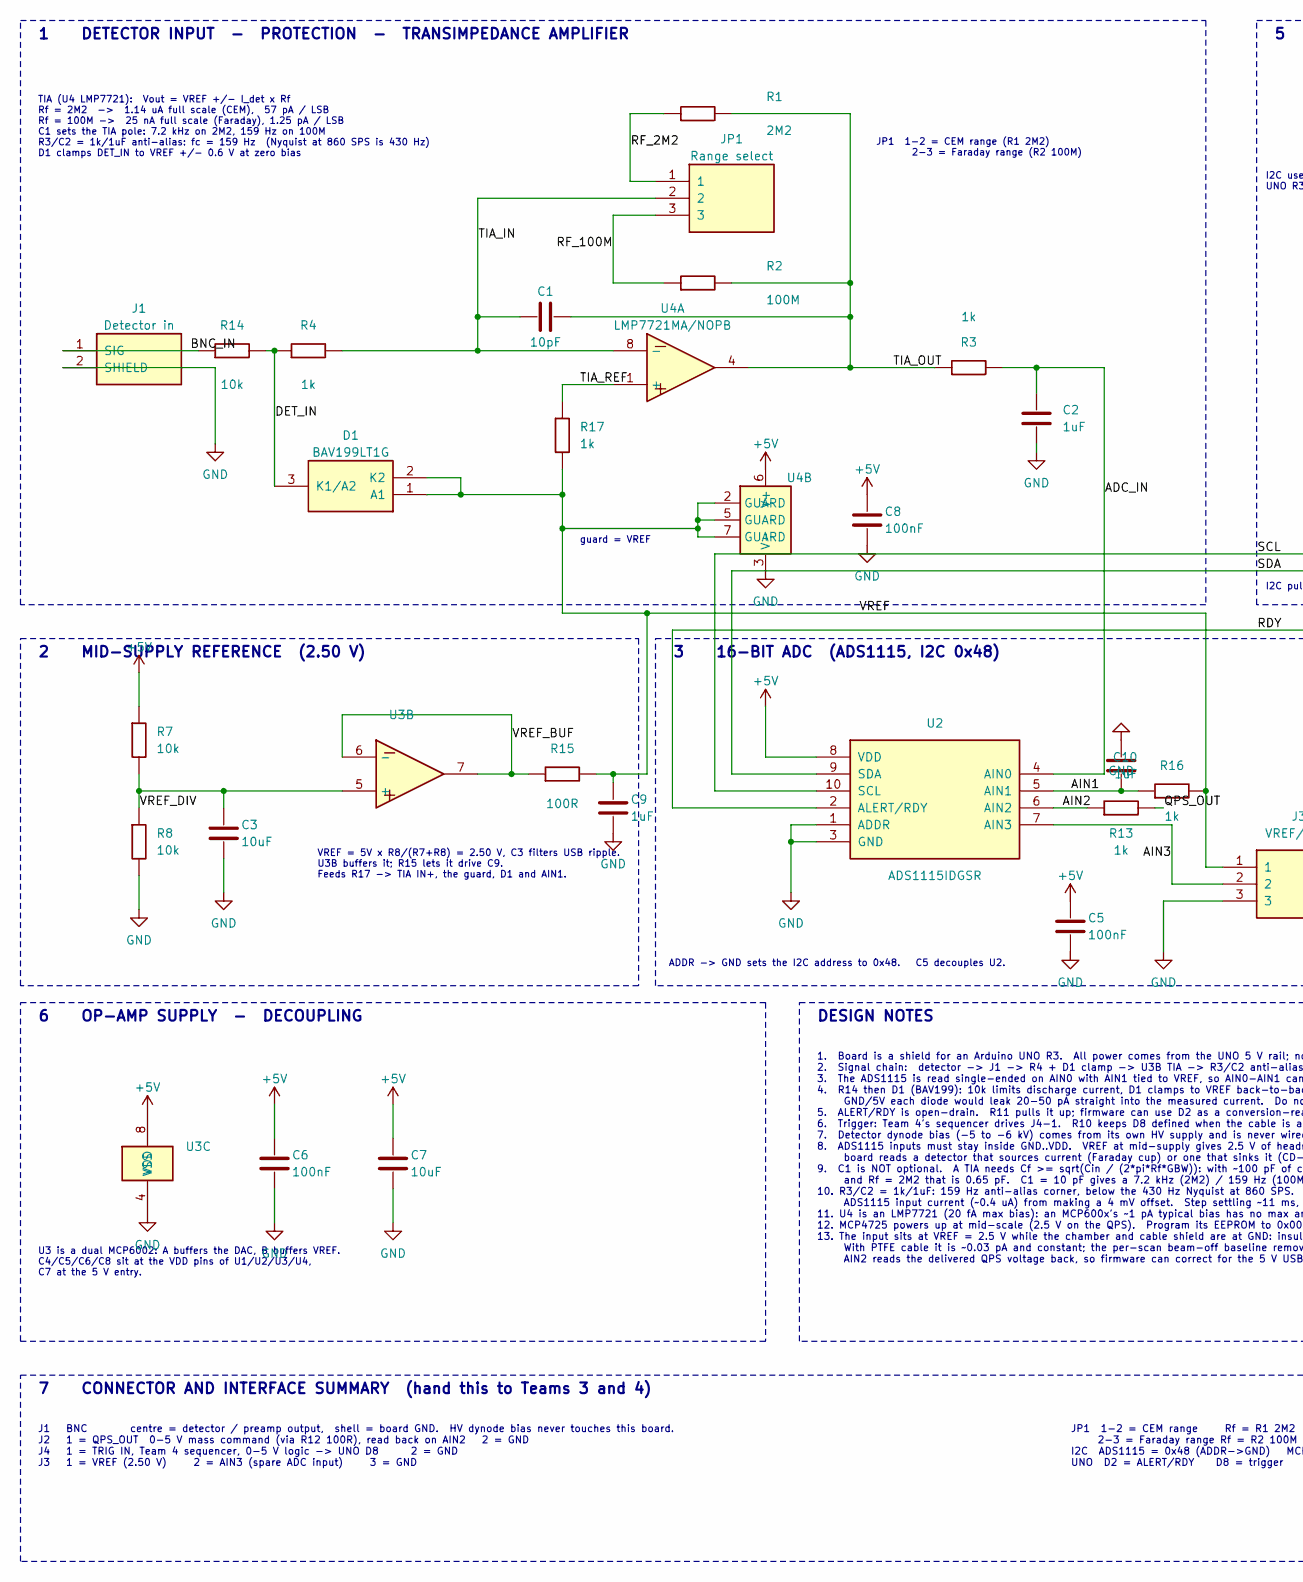
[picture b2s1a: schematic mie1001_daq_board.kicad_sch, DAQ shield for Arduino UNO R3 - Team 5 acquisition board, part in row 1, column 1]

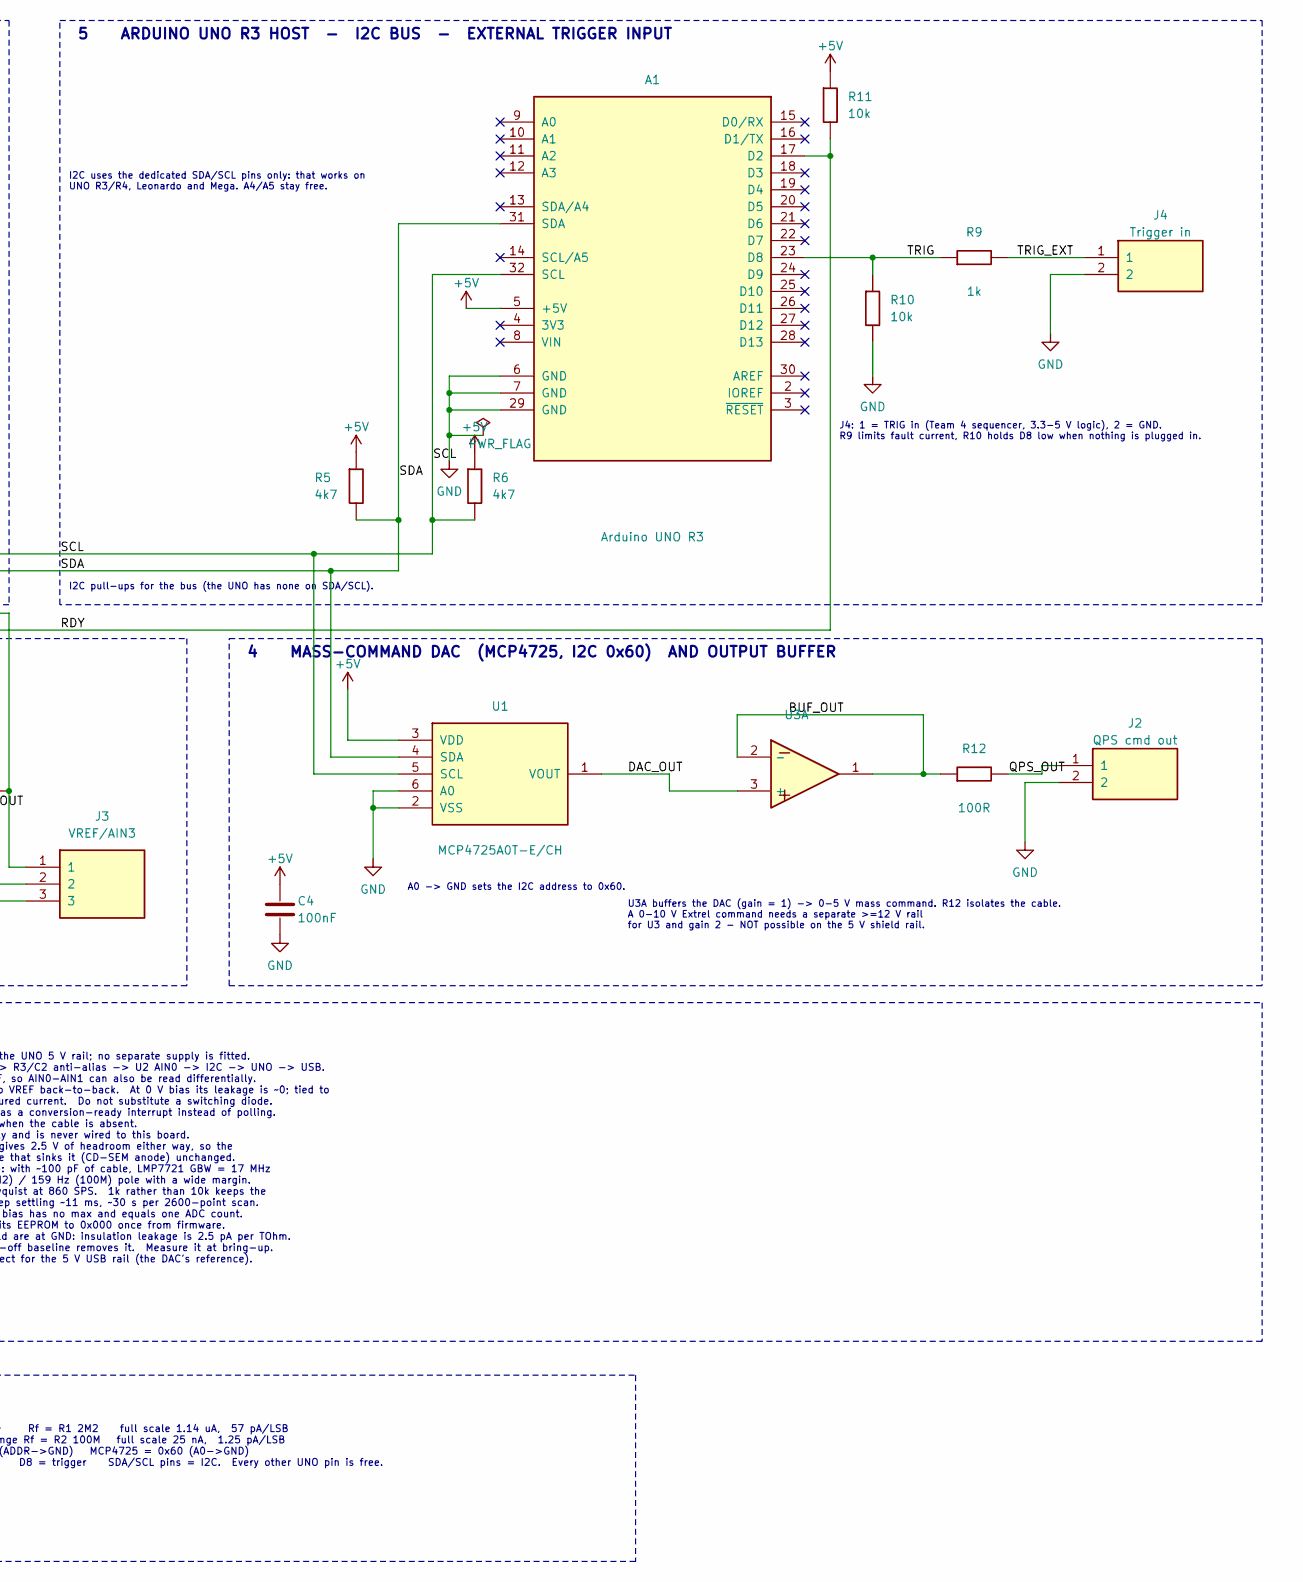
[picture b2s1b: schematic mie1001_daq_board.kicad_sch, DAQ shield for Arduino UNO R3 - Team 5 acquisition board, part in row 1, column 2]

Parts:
A1: Arduino UNO R3; Arduino_UNO_R3; Rating Arduino UNO R3; MPN A000066; Digi-Key P/N 1050-1024-ND
C1: 10pF; C_0603_1608Metric; Rating 10pF C0G 50V 0603; MPN GRM1885C1H100JA01D; Digi-Key P/N 490-1403-1-ND
C2, C9, C10: 1uF; C_0603_1608Metric; Rating 1uF X5R 50V 0603; MPN CL10A105KB8NNNC; Digi-Key P/N 1276-1860-1-ND
C3, C7: 10uF; C_0805_2012Metric; Rating 10uF X5R 25V 0805; MPN CL21A106KAYNNNE; Digi-Key P/N 1276-2891-1-ND
C4, C5, C6, C8: 100nF; C_0603_1608Metric; Rating 100nF X7R 50V 0603; MPN CL10B104KB8NNNC; Digi-Key P/N 1276-1000-1-ND
D1: BAV199LT1G; SOT-23; Rating BAV199LT1G; MPN BAV199LT1G; Digi-Key P/N BAV199LT1GOSCT-ND
J1: Detector in; BNC_Amphenol_031-6575_Horizontal; Rating Detector in, BNC; MPN 031-6575; Digi-Key P/N ARF2111-ND
J2: QPS cmd out; TerminalBlock_Phoenix_PT-1,5-2-3.5-H_1x02_P3.50mm_Horizontal; Rating QPS mass cmd out; MPN 1984617; Digi-Key P/N 277-1721-ND
J3: VREF/AIN3; PinHeader_1x03_P2.54mm_Vertical; Rating VREF / AIN3 / GND; MPN PRPC040SAAN-RC; Digi-Key P/N S1011EC-40-ND
J4: Trigger in; TerminalBlock_Phoenix_PT-1,5-2-3.5-H_1x02_P3.50mm_Horizontal; Rating Trigger in; MPN 1984617; Digi-Key P/N 277-1721-ND
JP1: Range select; PinHeader_1x03_P2.54mm_Vertical; Rating TIA range select; MPN PRPC040SAAN-RC; Digi-Key P/N S1011EC-40-ND
R1: 2M2; R_0603_1608Metric; Rating 2M2 1% 0603; MPN RC0603FR-072M2L; Digi-Key P/N YAG3329CT-ND
R2: 100M; R_1206_3216Metric; Rating 100M 1% 1206; MPN HVCB1206FKC100M; Digi-Key P/N HVCB1206FKC100MCT-ND
R3, R4, R9, R13, R16, R17: 1k; R_0603_1608Metric; Rating 1k 1% 0603; MPN RC0603FR-071KL; Digi-Key P/N 311-1.00KHRCT-ND
R5, R6: 4k7; R_0603_1608Metric; Rating 4k7 1% 0603; MPN RC0603FR-074K7L; Digi-Key P/N 311-4.70KHRCT-ND
R7, R8, R10, R11: 10k; R_0603_1608Metric; Rating 10k 1% 0603; MPN RC0603FR-0710KL; Digi-Key P/N 311-10.0KHRCT-ND
R12, R15: 100R; R_0603_1608Metric; Rating 100R 1% 0603; MPN RC0603FR-07100RL; Digi-Key P/N 311-100HRCT-ND
R14: 10k; R_0603_1608Metric; Rating 10k 1% 0603 anti-surge; MPN ERJ-PA3F1002V; Digi-Key P/N P10KBYCT-ND
U1: MCP4725A0T-E/CH; SOT-23-6; Rating MCP4725A0T-E/CH; MPN MCP4725A0T-E/CH; Digi-Key P/N MCP4725A0T-E/CHCT-ND
U2: ADS1115IDGSR; MSOP-10_3x3mm_P0.5mm; Rating ADS1115IDGSR; MPN ADS1115IDGSR; Digi-Key P/N 296-38849-1-ND
U3: MCP6002-I/SN; SOIC-8_3.9x4.9mm_P1.27mm; Rating MCP6002-I/SN; MPN MCP6002-I/SN; Digi-Key P/N MCP6002-I/SN-ND
U4: LMP7721MA/NOPB; SOIC-8_3.9x4.9mm_P1.27mm; Rating LMP7721MA/NOPB; MPN LMP7721MA/NOPB; Digi-Key P/N LMP7721MA/NOPB-ND

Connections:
+5V: A1.5 (+5V), C4.1, C5.1, C6.1, C7.1, C8.1, R5.1, R6.1, R7.1, R11.1, U1.3 (VDD), U2.8 (VDD), U3.8 (VDD), U4.6 (V+)
/ADC_IN: C2.1, R3.2, U2.4 (AIN0)
/AIN1: C10.1, R16.1, U2.5 (AIN1)
/AIN2: R13.1, U2.6 (AIN2)
/AIN3: J3.2, U2.7 (AIN3)
/BNC_IN: J1.1 (SIG), R14.1
/BUF_OUT: R12.1, U3.1, U3.2 (-)
/DAC_OUT: U1.1 (VOUT), U3.3 (+)
/DET_IN: D1.3 (K1/A2), R4.1, R14.2
/QPS_OUT: J2.1, R12.2, R13.2
/RDY: A1.17 (D2), R11.2, U2.2 (ALERT/RDY)
/RF_2M2: JP1.1, R1.1
/RF_100M: JP1.3, R2.1
/SCL: A1.32 (SCL), R6.2, U1.5 (SCL), U2.10 (SCL)
/TIA_IN: C1.1, JP1.2, R4.2, U4.8 (-)
/TIA_OUT: C1.2, R1.2, R2.2, R3.1, U4.4
/TIA_REF: R17.1, U4.1 (+)
/TRIG: A1.23 (D8), R9.1, R10.1
/TRIG_EXT: J4.1, R9.2
/VREF: C9.1, D1.1 (A1), D1.2 (K2), J3.1, R15.2, R16.2, R17.2, U4.2 (GUARD), U4.5 (GUARD), U4.7 (GUARD)
/VREF_BUF: R15.1, U3.6 (-), U3.7
/VREF_DIV: C3.1, R7.2, R8.1, U3.5 (+)

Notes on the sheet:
1 DETECTOR INPUT - PROTECTION - TRANSIMPEDANCE AMPLIFIER
guard = VREF
JP1 1-2 = CEM range (R1 2M2) 2-3 = Faraday range (R2 100M)
TIA (U4 LMP7721): Vout = VREF +/- I_det x Rf Rf = 2M2 -> 1.14 uA full scale (CEM), 57 pA / LSB Rf = 100M -> 25 nA full scale (Faraday), 1.25 pA / LSB C1 sets the TIA pole: 7.2 kHz on 2M2, 159 Hz on 100M R3/C2 = 1k/1uF anti-alias: fc = 159 Hz (Nyquist at 860 SPS is 430 Hz) D1 clamps DET_IN to VREF +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
5 ARDUINO UNO R3 HOST - I2C BUS - EXTERNAL TRIGGER INPUT
I2C uses the dedicated SDA/SCL pins only: that works on UNO R3/R4, Leonardo and Mega. A4/A5 stay free.
I2C pull-ups for the bus (the UNO has none on SDA/SCL).
J4: 1 = TRIG in (Team 4 sequencer, 3.3-5 V logic), 2 = GND. R9 limits fault current, R10 holds D8 low when nothing is plugged in.
2 MID-SUPPLY REFERENCE (2.50 V)
VREF = 5V x R8/(R7+R8) = 2.50 V, C3 filters USB ripple. U3B buffers it; R15 lets it drive C9. Feeds R17 -> TIA IN+, the guard, D1 and AIN1.
3 16-BIT ADC (ADS1115, I2C 0x48)
ADDR -> GND sets the I2C address to 0x48. C5 decouples U2.
4 MASS-COMMAND DAC (MCP4725, I2C 0x60) AND OUTPUT BUFFER
A0 -> GND sets the I2C address to 0x60.
U3A buffers the DAC (gain = 1) -> 0-5 V mass command. R12 isolates the cable. A 0-10 V Extrel command needs a separate >=12 V rail for U3 and gain 2 - NOT possible on the 5 V shield rail.
6 OP-AMP SUPPLY - DECOUPLING
U3 is a dual MCP6002: A buffers the DAC, B buffers VREF. C4/C5/C6/C8 sit at the VDD pins of U1/U2/U3/U4, C7 at the 5 V entry.
DESIGN NOTES
1. Board is a shield for an Arduino UNO R3. All power comes from the UNO 5 V rail; no separate supply is fitted. 2. Signal chain: detector -> J1 -> R4 + D1 clamp -> U3B TIA -> R3/C2 anti-alias -> U2 AIN0 -> I2C -> UNO -> USB. 3. The ADS1115 is read single-ended on AIN0 with AIN1 tied to VREF, so AI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
7 CONNECTOR AND INTERFACE SUMMARY (hand this to Teams 3 and 4)
J1 BNC centre = detector / preamp output, shell = board GND. HV dynode bias never touches this board. J2 1 = QPS_OUT 0-5 V mass command (via R12 100R), read back on AIN2 2 = GND J4 1 = TRIG IN, Team 4 sequencer, 0-5 V logic -> UNO D8 2 = GND J3 1 = VREF (2.50 V) 2 = AIN3 (spare ADC input) 3 = GND
JP1 1-2 = CEM range Rf = R1 2M2 full scale 1.14 uA, 57 pA/LSB 2-3 = Faraday range Rf = R2 100M full scale 25 nA, 1.25 pA/LSB I2C ADS1115 = 0x48 (ADDR->GND) MCP4725 = 0x60 (A0->GND) UNO D2 = ALERT/RDY D8 = trigger SDA/SCL pins = I2C. Every other UNO pin is free.

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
